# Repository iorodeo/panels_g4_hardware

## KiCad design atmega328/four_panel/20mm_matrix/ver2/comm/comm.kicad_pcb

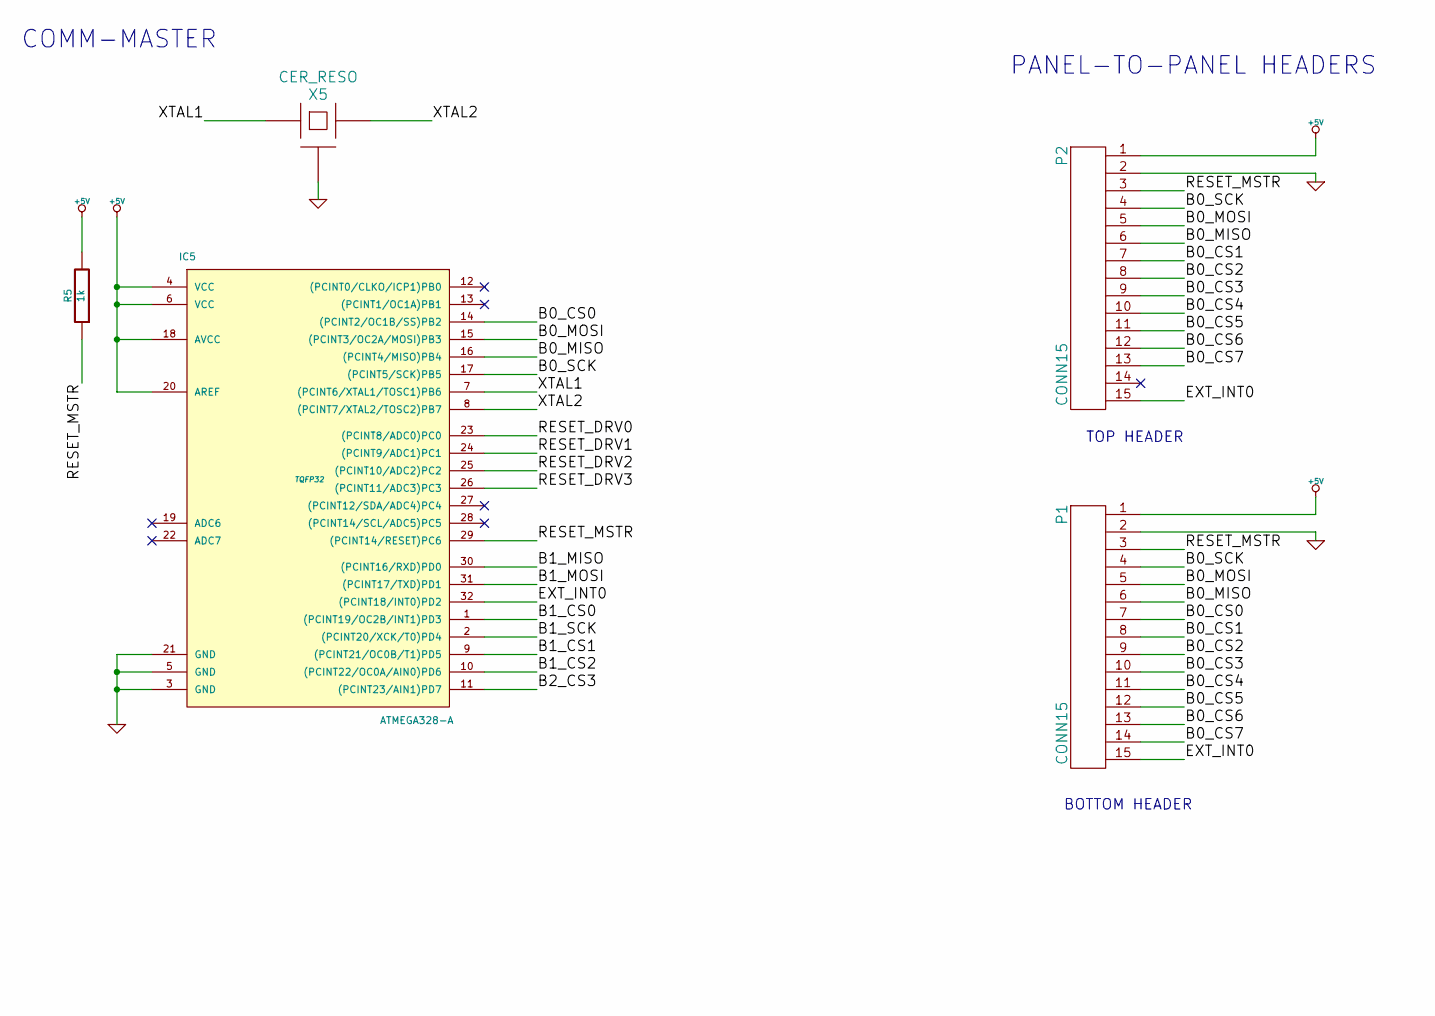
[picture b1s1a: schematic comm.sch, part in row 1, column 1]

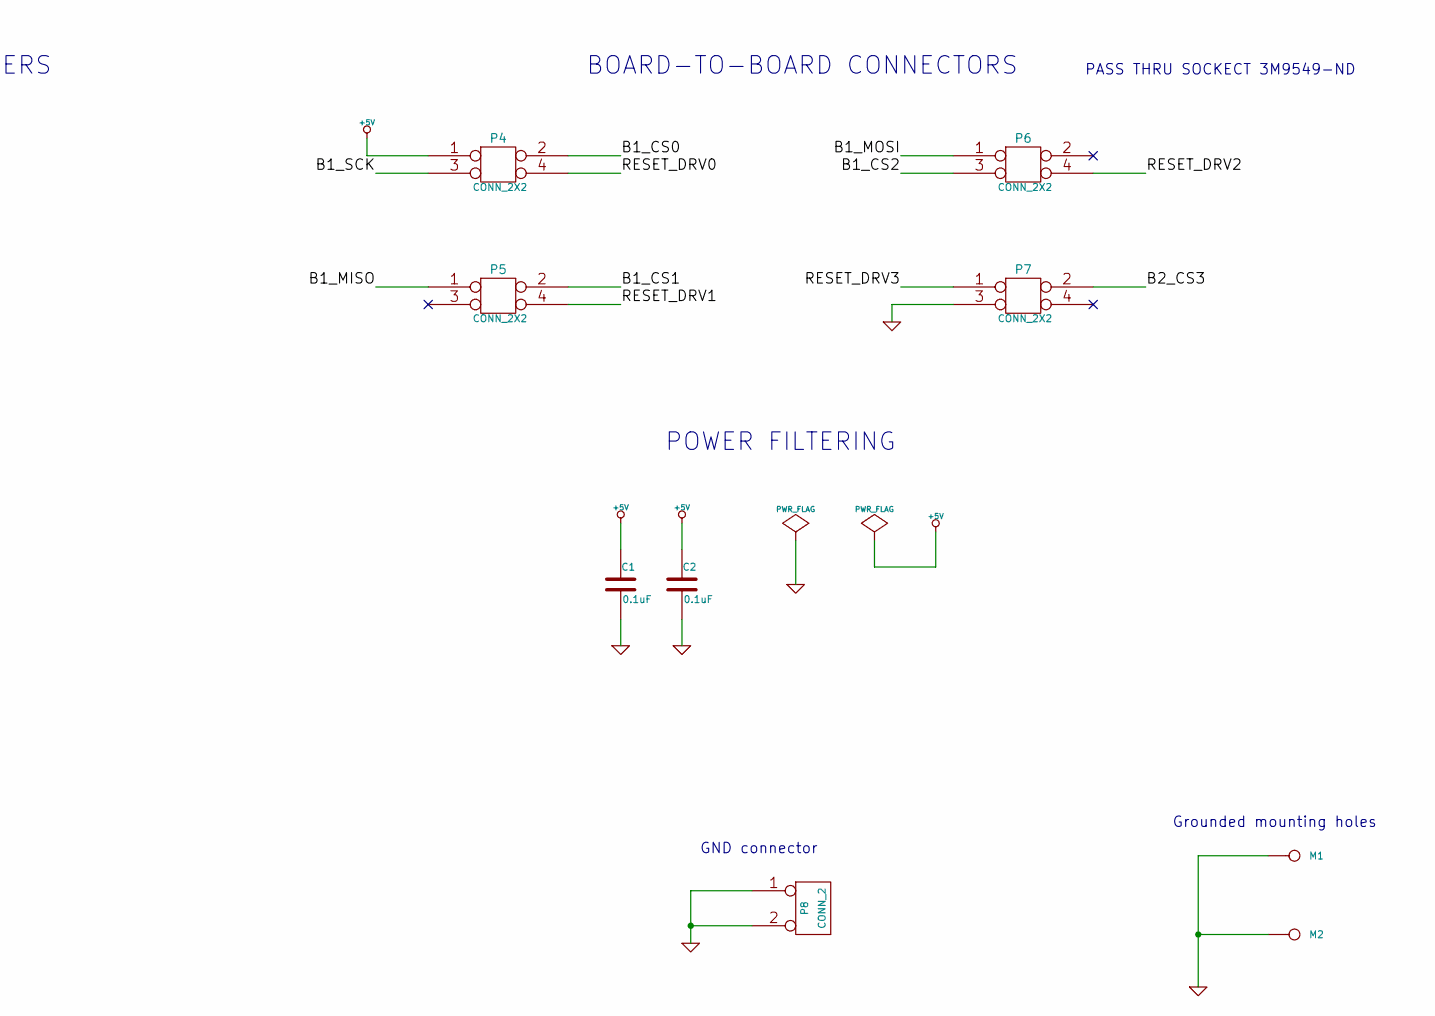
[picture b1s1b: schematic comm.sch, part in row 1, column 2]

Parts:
C1, C2: 0.1uF
IC5: ATMEGA328-A; TQFP32
M1, M2: CONN_1
P1, P2: CONN15
P4, P5, P6, P7: CONN_2X2
P8: CONN_2
R5: 1k
X5: CER_RESO

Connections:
+5V: C1.1, C2.1, IC5.4 (VCC), IC5.6 (VCC), IC5.18 (AVCC), IC5.20 (AREF), P1.1, P2.1, P4.1, R5.2
/B0_CS0: IC5.14 ((PCINT2/OC1B/SS)PB2), P1.7
/B0_CS1: P1.8, P2.7
/B0_CS2: P1.9, P2.8
/B0_CS3: P1.10, P2.9
/B0_CS4: P1.11, P2.10
/B0_CS5: P1.12, P2.11
/B0_CS6: P1.13, P2.12
/B0_CS7: P1.14, P2.13
/B0_MISO: IC5.16 ((PCINT4/MISO)PB4), P1.6, P2.6
/B0_MOSI: IC5.15 ((PCINT3/OC2A/MOSI)PB3), P1.5, P2.5
/B0_SCK: IC5.17 ((PCINT5/SCK)PB5), P1.4, P2.4
/B1_CS0: IC5.1 ((PCINT19/OC2B/INT1)PD3), P4.2
/B1_CS1: IC5.9 ((PCINT21/OC0B/T1)PD5), P5.2
/B1_CS2: IC5.10 ((PCINT22/OC0A/AIN0)PD6), P6.3
/B1_MISO: IC5.30 ((PCINT16/RXD)PD0), P5.1
/B1_MOSI: IC5.31 ((PCINT17/TXD)PD1), P6.1
/B1_SCK: IC5.2 ((PCINT20/XCK/T0)PD4), P4.3
/B2_CS3: IC5.11 ((PCINT23/AIN1)PD7), P7.2
/EXT_INT0: IC5.32 ((PCINT18/INT0)PD2), P1.15, P2.15
/RESET_DRV0: IC5.23 ((PCINT8/ADC0)PC0), P4.4
/RESET_DRV1: IC5.24 ((PCINT9/ADC1)PC1), P5.4
/RESET_DRV2: IC5.25 ((PCINT10/ADC2)PC2), P6.4
/RESET_DRV3: IC5.26 ((PCINT11/ADC3)PC3), P7.1
/RESET_MSTR: IC5.29 ((PCINT14/RESET)PC6), P1.3, P2.3, R5.1
/XTAL1: IC5.7 ((PCINT6/XTAL1/TOSC1)PB6), X5.1
/XTAL2: IC5.8 ((PCINT7/XTAL2/TOSC2)PB7), X5.3
GND: C1.2, C2.2, IC5.3 (GND), IC5.5 (GND), IC5.21 (GND), M1.1, M2.1, P1.2, P2.2, P7.3, P8.1, P8.2 (PM), X5.2 (GND)

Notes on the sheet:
COMM-MASTER
PANEL-TO-PANEL HEADERS
BOTTOM HEADER
TOP HEADER
POWER FILTERING
BOARD-TO-BOARD CONNECTORS
GND connector
Grounded mounting holes
PASS THRU SOCKECT 3M9549-ND

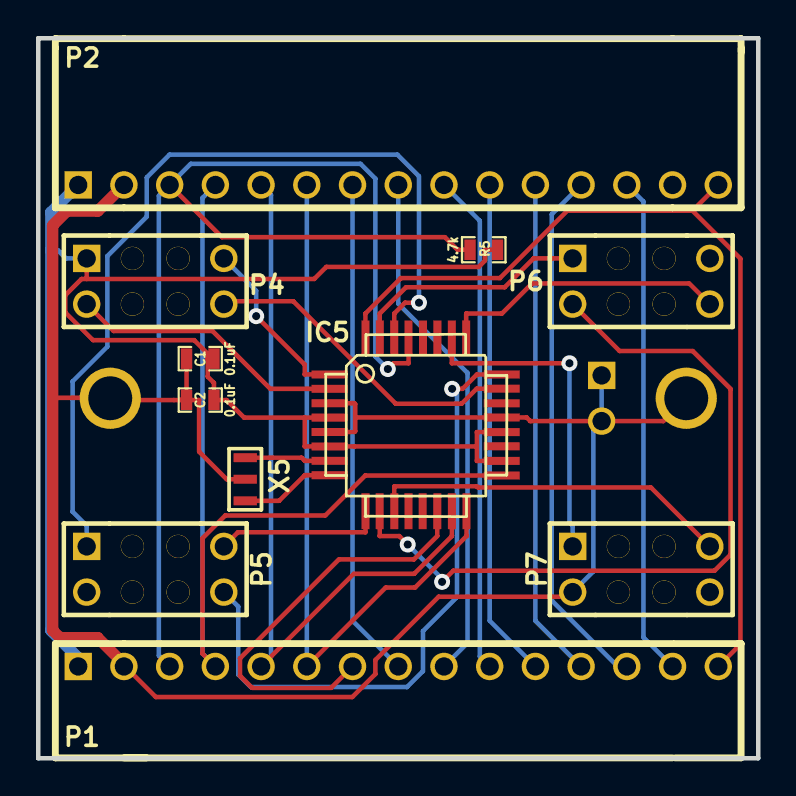
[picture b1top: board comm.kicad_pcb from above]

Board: 2 copper layers, 40.0 x 40.0 mm, 14 parts (1 on the bottom side), 28 nets.

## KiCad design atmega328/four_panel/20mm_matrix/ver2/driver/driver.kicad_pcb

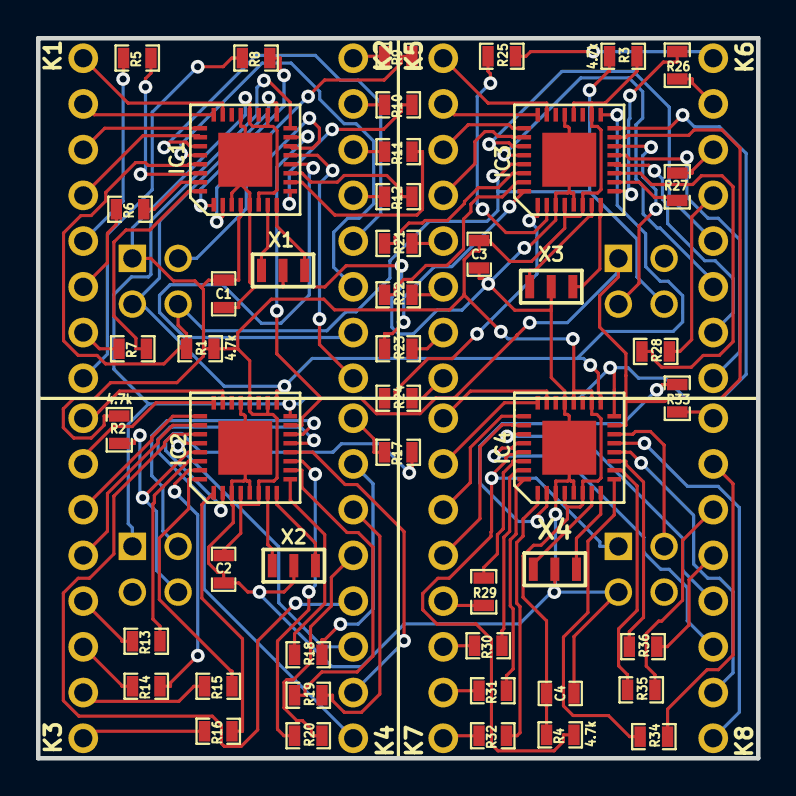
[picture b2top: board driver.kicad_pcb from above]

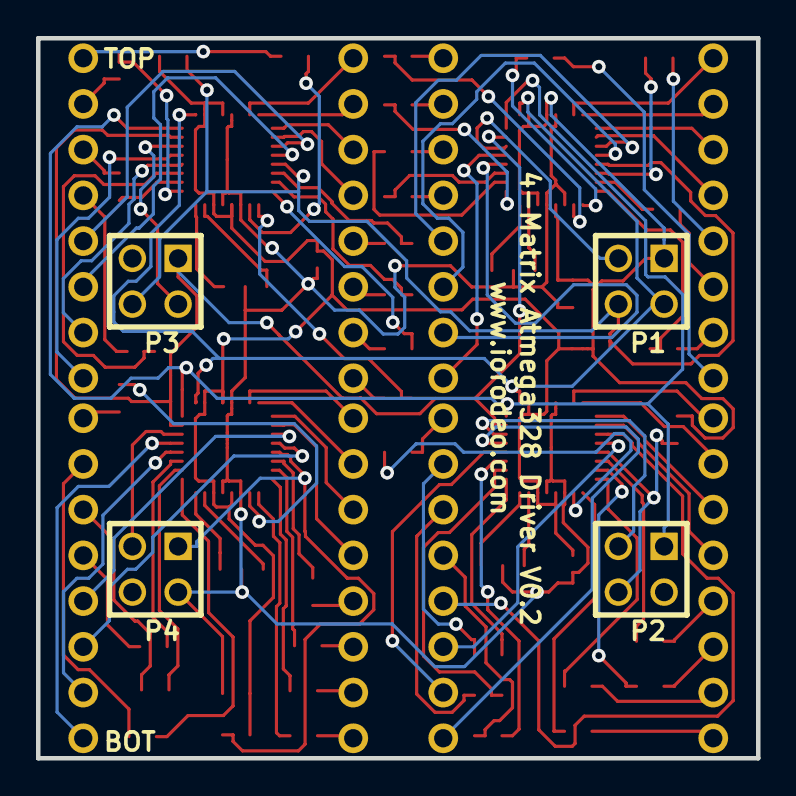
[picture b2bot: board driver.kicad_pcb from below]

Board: 2 copper layers, 40.0 x 40.0 mm, 56 parts (4 on the bottom side), 116 nets.

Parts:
C1, C2, C3, C4: 0.1uF; SM0603_Capa
IC1, IC2, IC3, IC4: ATMEGA328P-M; QFN32
MATRIX1, MATRIX2, MATRIX3, MATRIX4: LED_8X8; LED_MATRIX_20MM_8x8
P1, P2, P3, P4: CONN_2X2; PIN_ARRAY_2X2
R1, R2, R3, R4: 4.7k; SM0603_Resistor
R5, R6, R7, R8, R9, R10, R11, R12, R13, R14, R15, R16, R17, R18, R19, R20, R21, R22, R23, R24, R25, R26, R27, R28, R29, R30, R31, R32, R33, R34, R35, R36: 180; SM0603_Resistor
X1, X2, X3, X4: CER_RESO

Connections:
+5V: C1.1, C2.1, C3.1, C4.1, IC1.4, IC1.6, IC1.18, IC1.20, IC2.4, IC2.6, IC2.18, IC2.20, IC3.4, IC3.6, IC3.18, IC3.20, IC4.4, IC4.6, IC4.18, IC4.20, P1.1, R1.2, R2.2, R3.2, R4.2
/COL0_DRV0: IC1.30, R5.1
/COL0_DRV1: IC2.30, R13.1
/COL0_DRV2: IC3.30, R21.1
/COL0_DRV3: IC4.30, R29.1
/COL1_DRV0: IC1.31, R6.1
/COL1_DRV1: IC2.31, R14.1
/COL1_DRV2: IC3.31, R22.1
/COL1_DRV3: IC4.31, R30.1
/COL2_DRV0: IC1.32, R7.1
/COL2_DRV1: IC2.32, R15.1
/COL2_DRV2: IC3.32, R23.1
/COL2_DRV3: IC4.32, R31.1
/COL3_DRV0: IC1.1, R8.1
/COL3_DRV1: IC2.1, R16.1
/COL3_DRV2: IC3.1, R24.1
/COL3_DRV3: IC4.1, R32.1
/COL4_DRV0: IC1.2, R9.1
/COL4_DRV1: IC2.2, R17.1
/COL4_DRV2: IC3.2, R25.1
/COL4_DRV3: IC4.2, R33.1
/COL5_DRV0: IC1.9, R10.1
/COL5_DRV1: IC2.9, R18.1
/COL5_DRV2: IC3.9, R26.1
/COL5_DRV3: IC4.9, R34.1
/COL6_DRV0: IC1.10, R11.1
/COL6_DRV1: IC2.10, R19.1
/COL6_DRV2: IC3.10, R27.1
/COL6_DRV3: IC4.10, R35.1
/COL7_DRV0: IC1.11, R12.1
/COL7_DRV1: IC2.11, R20.1
/COL7_DRV2: IC3.11, R28.1
/COL7_DRV3: IC4.11, R36.1
/CS0: IC1.14, P1.3
/CS1: IC2.14, P2.3
/CS2: IC3.14, P3.2
/CS3: IC4.14, P4.3
/MISO: IC1.16, IC2.16, IC3.16, IC4.16, P2.1
/MOSI: IC1.15, IC2.15, IC3.15, IC4.15, P3.1
/RESET_DRV0: IC1.29, IC3.29, P1.4, P3.4, R1.1, R3.1
/RESET_DRV1: IC2.29, P2.4, R2.1
/RESET_DRV3: IC4.29, P4.1, R4.1
/ROW0_DRV0: IC1.23, MATRIX1.1
/ROW0_DRV1: IC2.23, MATRIX2.1
/ROW0_DRV2: IC3.23, MATRIX3.1
/ROW0_DRV3: IC4.23, MATRIX4.1
/ROW1_DRV0: IC1.24, MATRIX1.2
/ROW1_DRV1: IC2.24, MATRIX2.2
/ROW1_DRV2: IC3.24, MATRIX3.2
/ROW1_DRV3: IC4.24, MATRIX4.2
/ROW2_DRV0: IC1.25, MATRIX1.3
/ROW2_DRV1: IC2.25, MATRIX2.3
/ROW2_DRV2: IC3.25, MATRIX3.3
/ROW2_DRV3: IC4.25, MATRIX4.3
/ROW3_DRV0: IC1.26, MATRIX1.4
/ROW3_DRV1: IC2.26, MATRIX2.4
/ROW3_DRV2: IC3.26, MATRIX3.4
/ROW3_DRV3: IC4.26, MATRIX4.4
/ROW4_DRV0: IC1.27, MATRIX1.12
/ROW4_DRV1: IC2.27, MATRIX2.12
/ROW4_DRV2: IC3.27, MATRIX3.12
/ROW4_DRV3: IC4.27, MATRIX4.12
/ROW5_DRV0: IC1.28, MATRIX1.11
/ROW5_DRV1: IC2.28, MATRIX2.11
/ROW5_DRV2: IC3.28, MATRIX3.11
/ROW5_DRV3: IC4.28, MATRIX4.11
/ROW6_DRV0: IC1.12, MATRIX1.10
/ROW6_DRV1: IC2.12, MATRIX2.10
/ROW6_DRV2: IC3.12, MATRIX3.10
/ROW6_DRV3: IC4.12, MATRIX4.10
/ROW7_DRV0: IC1.13, MATRIX1.9
/ROW7_DRV1: IC2.13, MATRIX2.9
/ROW7_DRV2: IC3.13, MATRIX3.9
/ROW7_DRV3: IC4.13, MATRIX4.9
/SCK: IC1.17, IC2.17, IC3.17, IC4.17, P1.2
/XTAL0_DRV0: IC1.7, X1.1
/XTAL0_DRV1: IC2.7, X2.1
/XTAL0_DRV2: IC3.7, X3.1
/XTAL0_DRV3: IC4.7, X4.1
/XTAL1_DRV0: IC1.8, X1.3
/XTAL1_DRV1: IC2.8, X2.3
/XTAL1_DRV2: IC3.8, X3.3
/XTAL1_DRV3: IC4.8, X4.3
GND: C1.2, C2.2, C3.2, C4.2, IC1.3, IC1.5, IC1.21, IC1.33, IC2.3, IC2.5, IC2.21, IC2.33, IC3.3, IC3.5, IC3.21, IC3.33, IC4.3, IC4.5, IC4.21, IC4.33, P4.2, X1.2, X2.2, X3.2, X4.2
unnamed: MATRIX4.13, R36.2
unnamed: MATRIX4.14, R35.2
unnamed: MATRIX4.15, R34.2
unnamed: MATRIX4.16, R33.2
unnamed: MATRIX1.8, R8.2
unnamed: MATRIX1.16, R9.2
unnamed: MATRIX1.15, R10.2
unnamed: MATRIX1.14, R11.2
unnamed: MATRIX1.13, R12.2
unnamed: MATRIX4.6, R30.2
unnamed: MATRIX4.7, R31.2
unnamed: MATRIX4.5, R29.2
unnamed: MATRIX4.8, R32.2
unnamed: MATRIX1.5, R5.2
unnamed: MATRIX1.6, R6.2
unnamed: MATRIX1.7, R7.2
unnamed: MATRIX2.15, R18.2
unnamed: MATRIX2.14, R19.2
unnamed: MATRIX2.13, R20.2
unnamed: MATRIX2.6, R14.2
unnamed: MATRIX2.7, R15.2
unnamed: MATRIX2.5, R13.2
unnamed: MATRIX2.8, R16.2
unnamed: MATRIX3.5, R21.2
unnamed: MATRIX2.16, R17.2
unnamed: MATRIX3.8, R24.2
unnamed: MATRIX3.6, R22.2
unnamed: MATRIX3.7, R23.2
unnamed: MATRIX3.16, R25.2
unnamed: MATRIX3.15, R26.2
unnamed: MATRIX3.14, R27.2
unnamed: MATRIX3.13, R28.2

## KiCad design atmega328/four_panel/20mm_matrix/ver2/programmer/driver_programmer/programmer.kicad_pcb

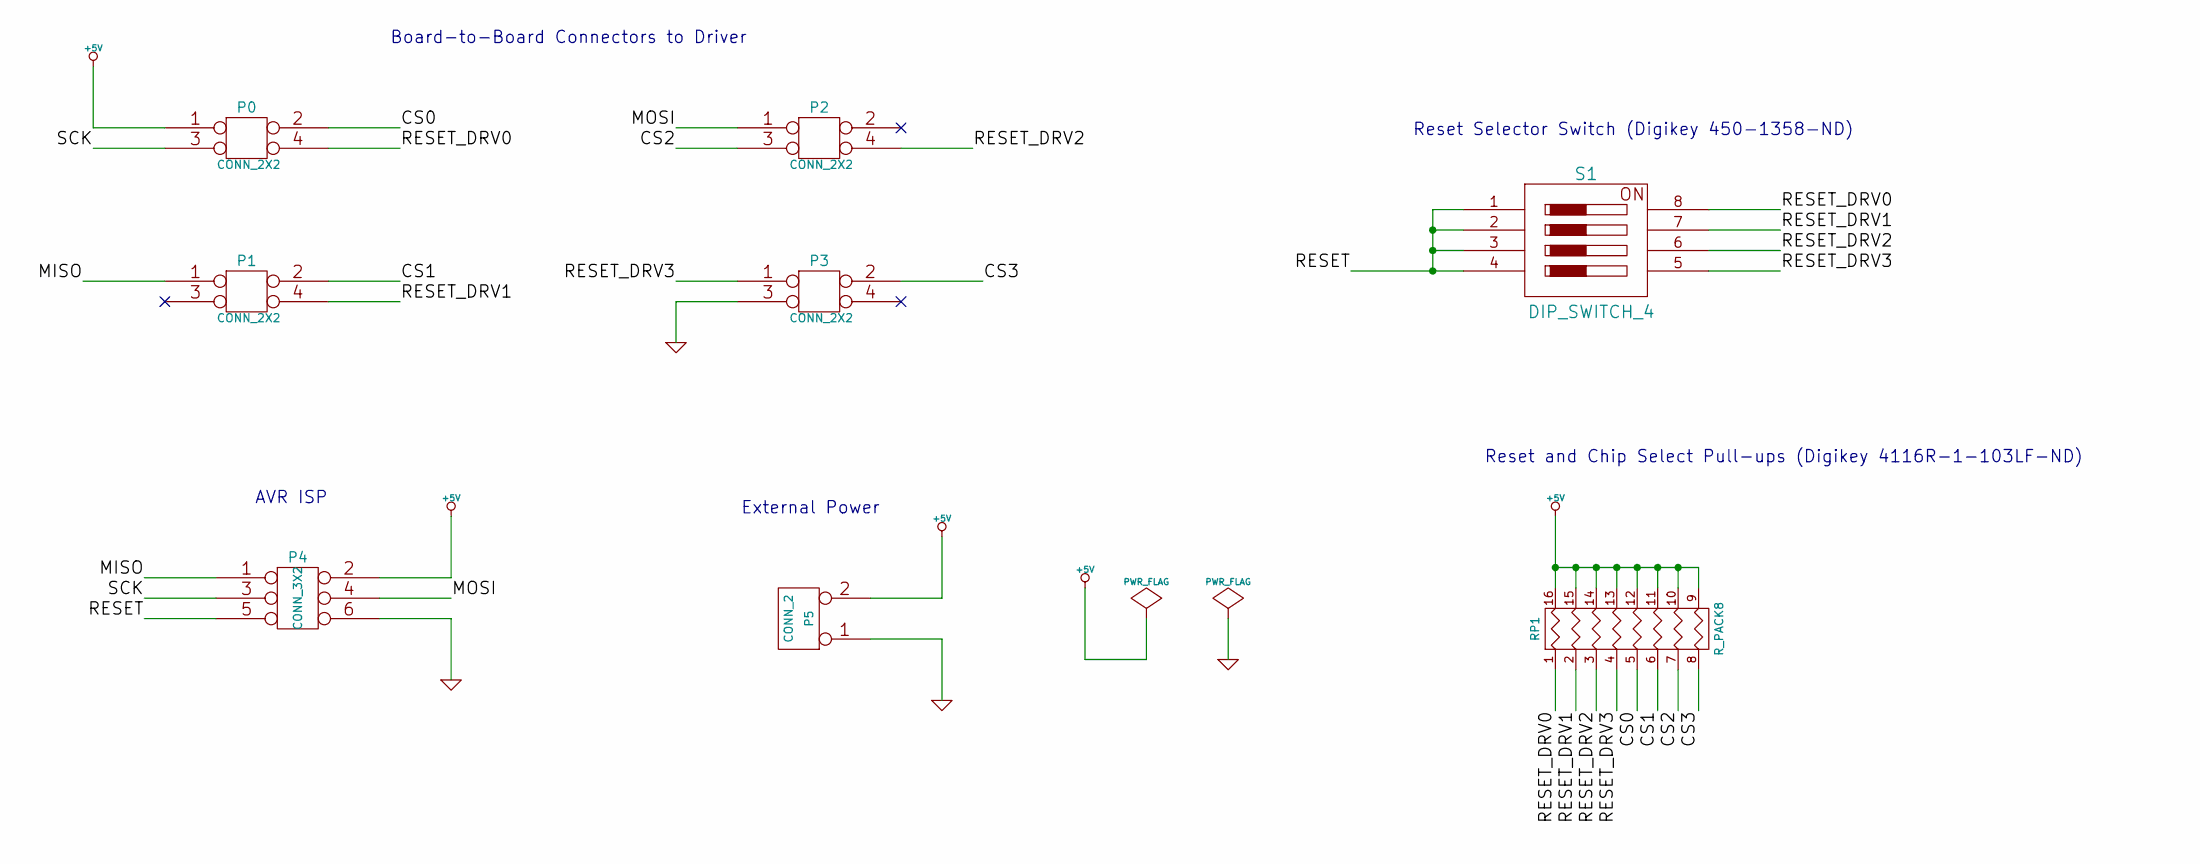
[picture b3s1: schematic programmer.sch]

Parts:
P0, P1, P2, P3: CONN_2X2
P4: CONN_3X2
P5: CONN_2
RP1: R_PACK8
S1: DIP_SWITCH_4

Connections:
+5V: P0.1, P4.2, P5.2 (PM), RP1.9 (R8), RP1.10 (R7), RP1.11 (R6), RP1.12 (R5), RP1.13 (R4), RP1.14 (R3), RP1.15 (R2), RP1.16 (R1)
/CS0: P0.2, RP1.5
/CS1: P1.2, RP1.6
/CS2: P2.3, RP1.7
/CS3: P3.2, RP1.8
/MISO: P1.1, P4.1
/MOSI: P2.1, P4.4
/RESET: P4.5, S1.1, S1.2, S1.3, S1.4
/RESET_DRV0: P0.4, RP1.1, S1.8
/RESET_DRV1: P1.4, RP1.2, S1.7
/RESET_DRV2: P2.4, RP1.3, S1.6
/RESET_DRV3: P3.1, RP1.4, S1.5
/SCK: P0.3, P4.3
GND: P3.3, P4.6, P5.1

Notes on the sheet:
AVR ISP
External Power
Board-to-Board Connectors to Driver
Reset and Chip Select Pull-ups (Digikey 4116R-1-103LF-ND)
Reset Selector Switch (Digikey 450-1358-ND)

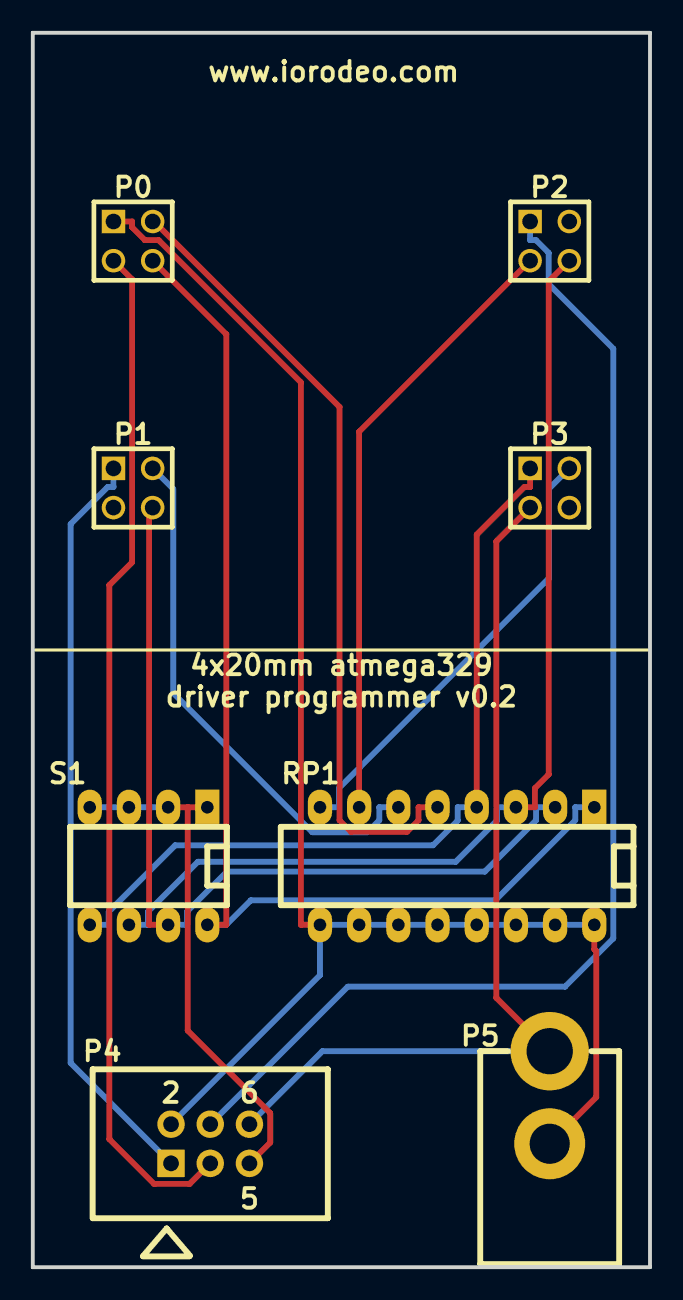
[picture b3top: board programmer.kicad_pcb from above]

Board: 2 copper layers, 40.0 x 80.0 mm, 8 parts (0 on the bottom side), 14 nets.

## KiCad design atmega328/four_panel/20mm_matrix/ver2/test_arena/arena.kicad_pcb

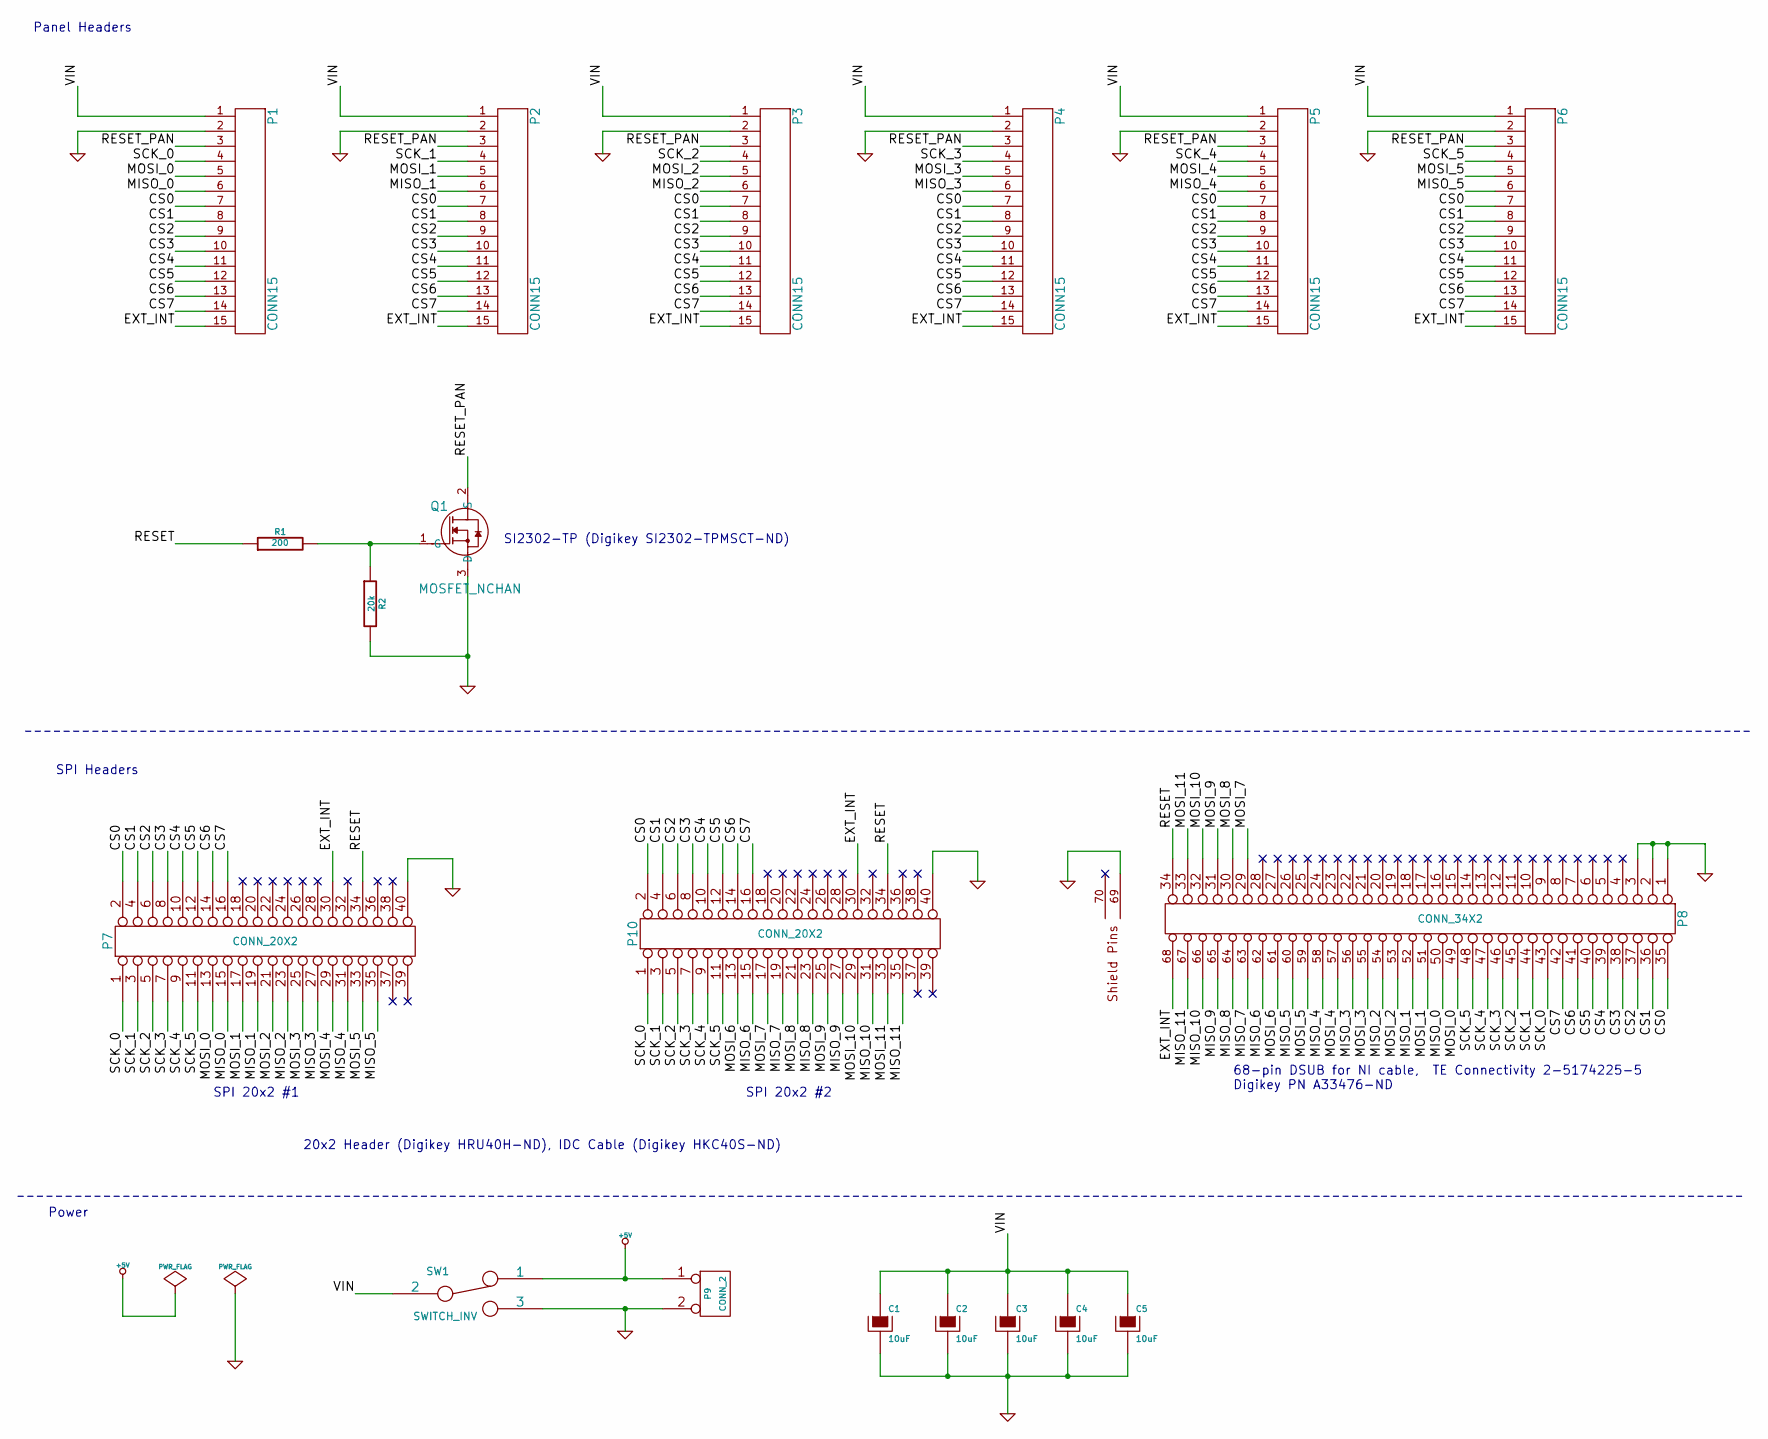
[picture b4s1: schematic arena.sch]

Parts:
C1, C2, C3, C4, C5: 10uF
P1, P2, P3, P4, P5, P6: CONN15
P7, P10: CONN_20X2
P8: CONN_34X2
P9: CONN_2
Q1: MOSFET_NCHAN
R1: 200
R2: 20k
SW1: SWITCH_INV

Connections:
+5V: P9.1, SW1.1
/CS0: P1.7, P2.7, P3.7, P4.7, P5.7, P6.7, P7.2, P8.35, P10.2
/CS1: P1.8, P2.8, P3.8, P4.8, P5.8, P6.8, P7.4, P8.36, P10.4
/CS2: P1.9, P2.9, P3.9, P4.9, P5.9, P6.9, P7.6, P8.37, P10.6
/CS3: P1.10, P2.10, P3.10, P4.10, P5.10, P6.10, P7.8, P8.38, P10.8
/CS4: P1.11, P2.11, P3.11, P4.11, P5.11, P6.11, P7.10, P8.39, P10.10
/CS5: P1.12, P2.12, P3.12, P4.12, P5.12, P6.12, P7.12, P8.40, P10.12
/CS6: P1.13, P2.13, P3.13, P4.13, P5.13, P6.13, P7.14, P8.41, P10.14
/CS7: P1.14, P2.14, P3.14, P4.14, P5.14, P6.14, P7.16, P8.42, P10.16
/EXT_INT: P1.15, P2.15, P3.15, P4.15, P5.15, P6.15, P7.30, P8.68, P10.30
/MISO_0: P1.6, P7.15, P8.50
/MISO_1: P2.6, P7.19, P8.52
/MISO_2: P3.6, P7.23, P8.54
/MISO_3: P4.6, P7.27, P8.56
/MISO_4: P5.6, P7.31, P8.58
/MISO_5: P6.6, P7.35, P8.60
/MISO_6: P8.62, P10.15
/MISO_7: P8.63, P10.19
/MISO_8: P8.64, P10.23
/MISO_9: P8.65, P10.27
/MISO_10: P8.66, P10.31
/MISO_11: P8.67, P10.35
/MOSI_0: P1.5, P7.13, P8.49
/MOSI_1: P2.5, P7.17, P8.51
/MOSI_2: P3.5, P7.21, P8.53
/MOSI_3: P4.5, P7.25, P8.55
/MOSI_4: P5.5, P7.29, P8.57
/MOSI_5: P6.5, P7.33, P8.59
/MOSI_6: P8.61, P10.13
/MOSI_7: P8.29, P10.17
/MOSI_8: P8.30, P10.21
/MOSI_9: P8.31, P10.25
/MOSI_10: P8.32, P10.29
/MOSI_11: P8.33, P10.33
/RESET: P7.34, P8.34, P10.34, R1.1
/RESET_PAN: P1.3, P2.3, P3.3, P4.3, P5.3, P6.3, Q1.2 (S)
/SCK_0: P1.4, P7.1, P8.43, P10.1
/SCK_1: P2.4, P7.3, P8.44, P10.3
/SCK_2: P3.4, P7.5, P8.45, P10.5
/SCK_3: P4.4, P7.7, P8.46, P10.7
/SCK_4: P5.4, P7.9, P8.47, P10.9
/SCK_5: P6.4, P7.11, P8.48, P10.11
/VIN: C1.1, C2.1, C3.1, C4.1, C5.1, P1.1, P2.1, P3.1, P4.1, P5.1, P6.1, SW1.2
GND: C1.2, C2.2, C3.2, C4.2, C5.2, P1.2, P2.2, P3.2, P4.2, P5.2, P6.2, P7.40, P8.1, P8.2, P8.3, P8.69, P9.2 (PM), P10.40, Q1.3 (D), R2.2, SW1.3
unnamed: Q1.1 (G), R1.2, R2.1

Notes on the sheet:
Power
Panel Headers
SPI Headers
20x2 Header (Digikey HRU40H-ND), IDC Cable (Digikey HKC40S-ND)
68-pin DSUB for NI cable, TE Connectivity 2-5174225-5 Digikey PN A33476-ND
SI2302-TP (Digikey SI2302-TPMSCT-ND)
SPI 20x2 #1
SPI 20x2 #2

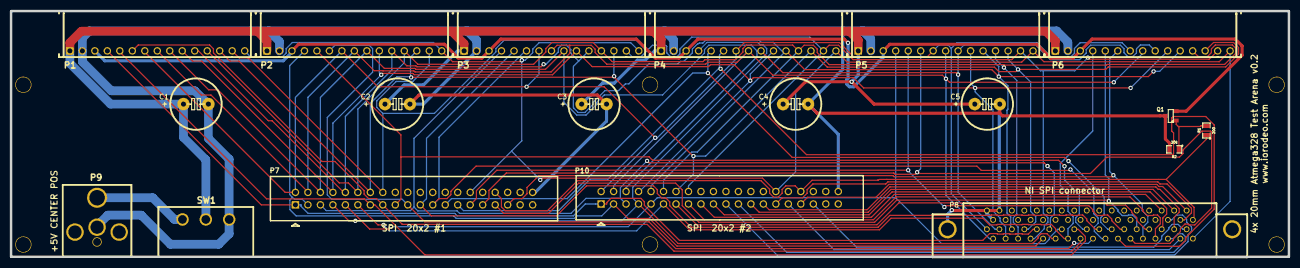
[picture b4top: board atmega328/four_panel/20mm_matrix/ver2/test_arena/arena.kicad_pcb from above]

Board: 2 copper layers, 260.0 x 50.0 mm, 25 parts (0 on the bottom side), 45 nets.

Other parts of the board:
M1, M2, M3, M4, M5, M6: VAL**; MOUNT_HOLE_4_40
